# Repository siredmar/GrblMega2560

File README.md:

# GrblMega2560
Shield for GRBL 1.0 based on Arduino Mega 2560

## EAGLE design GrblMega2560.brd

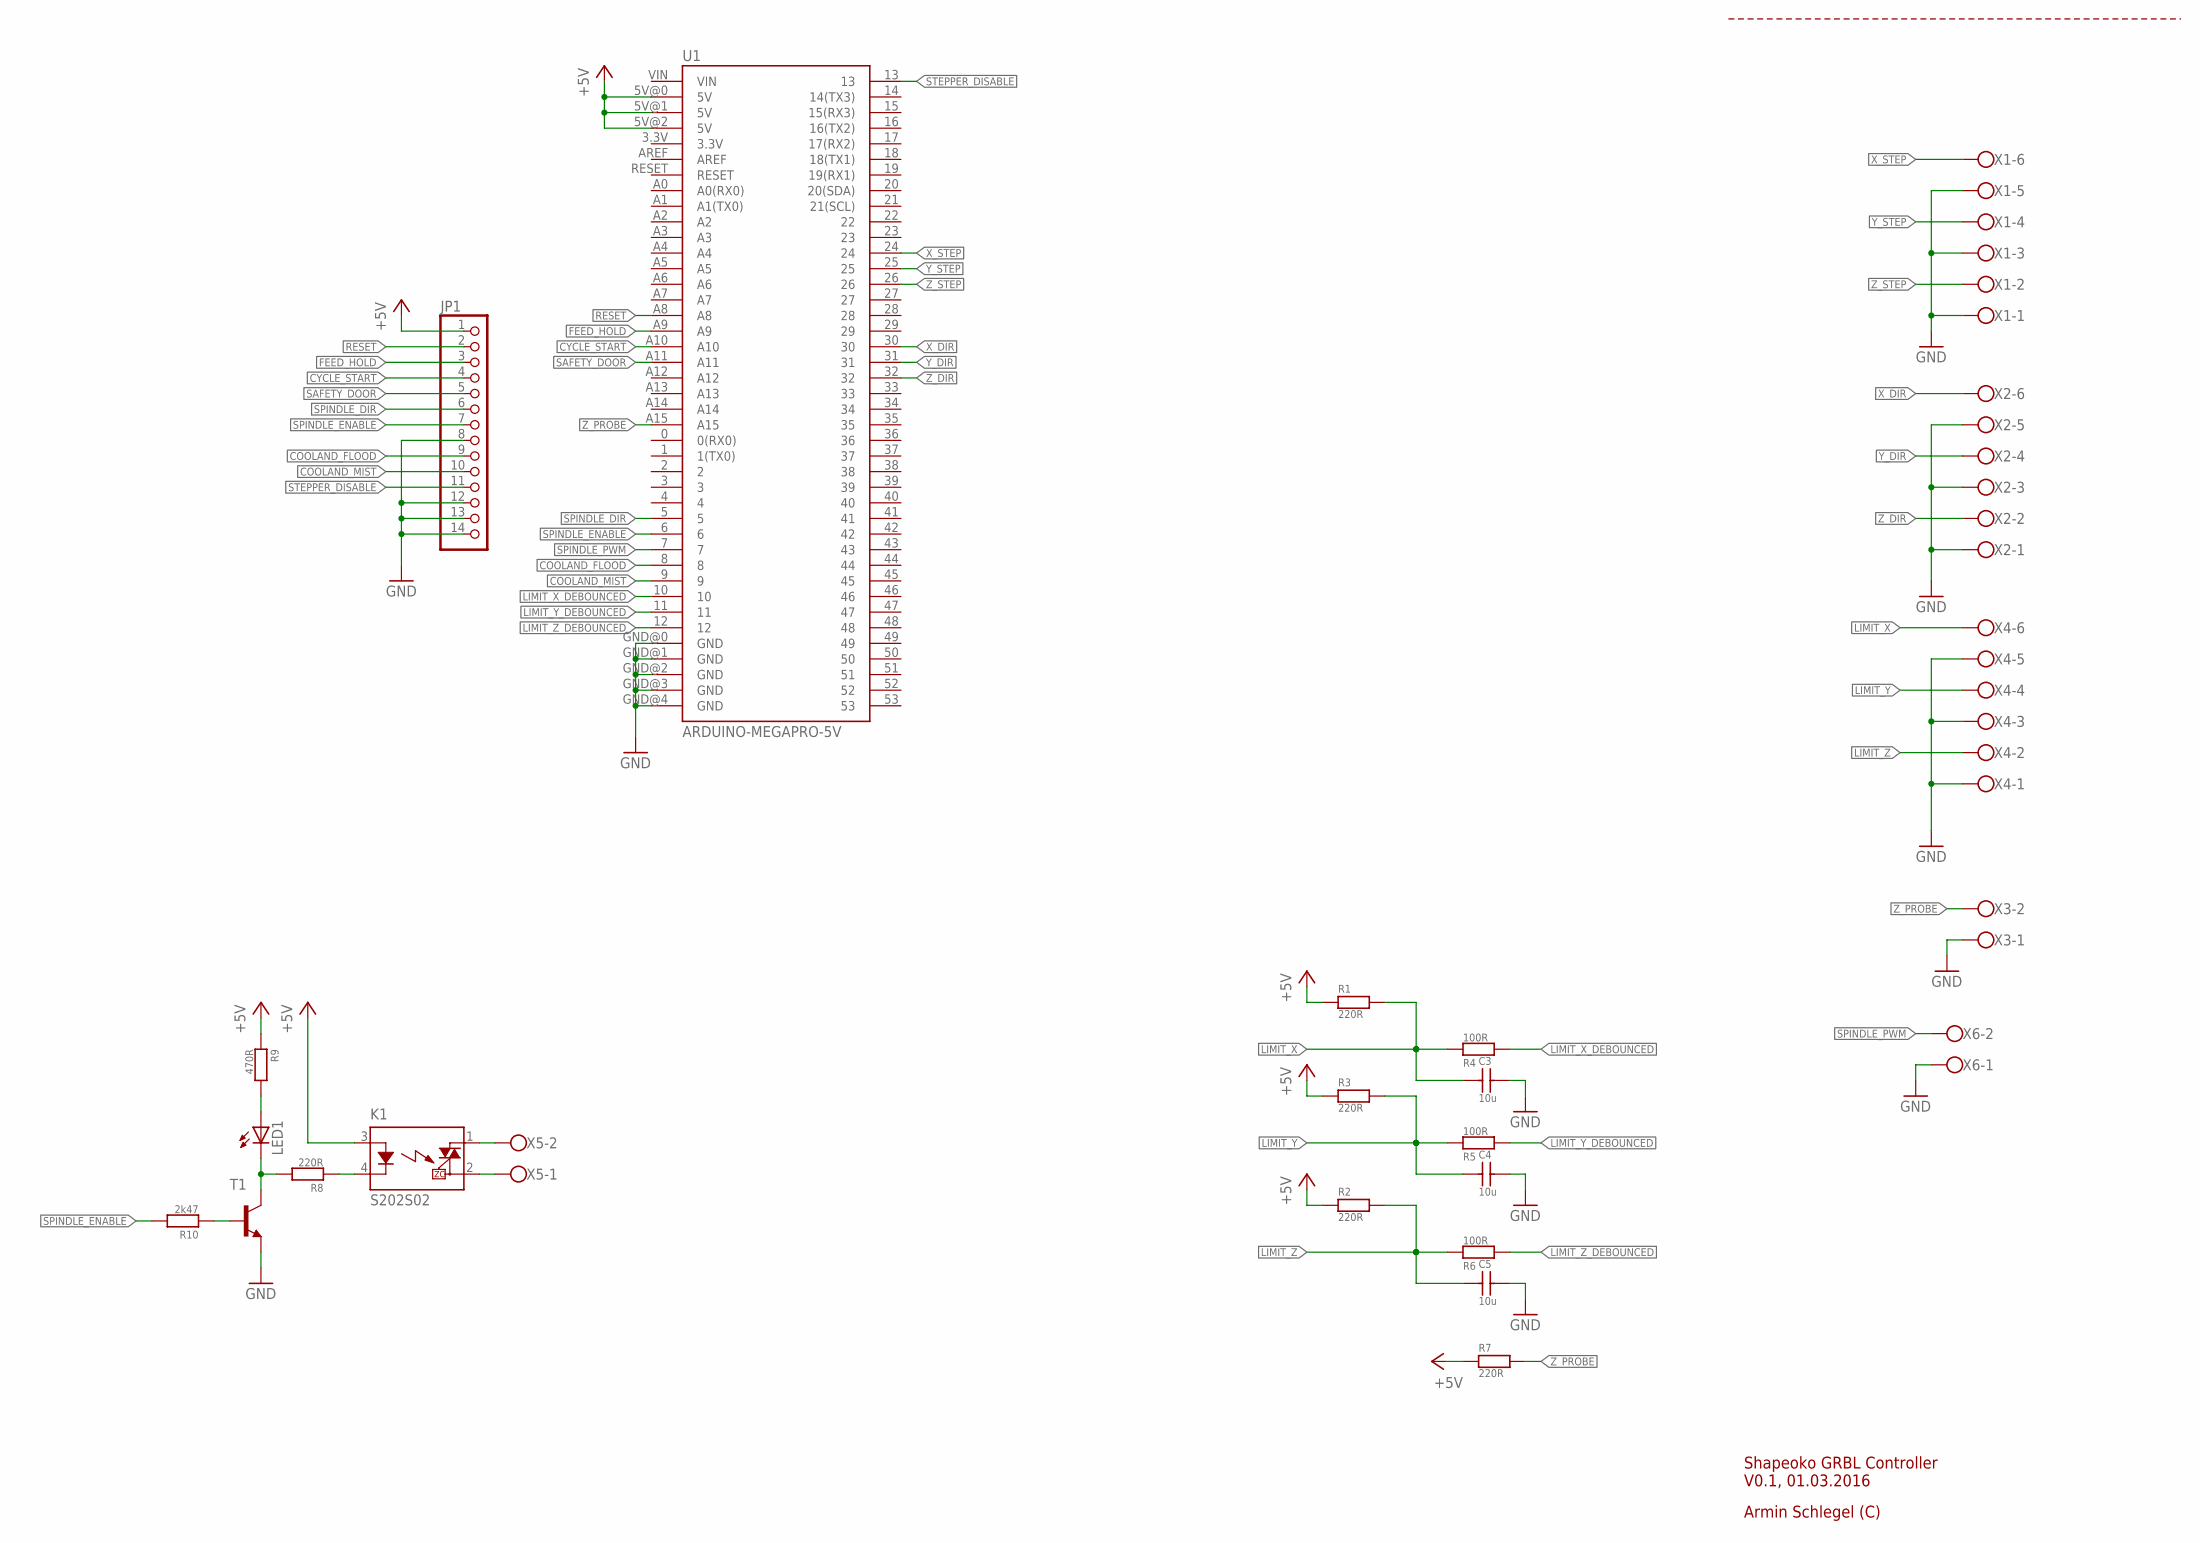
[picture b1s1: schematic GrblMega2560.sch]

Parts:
C3, C4, C5: 10u; C0805
JP1: PINHD-1X14; 1X14
K1: S202S02
LED1: LED3MM
R1, R2, R3, R7, R8: 220R; R0603
R4, R5, R6: 100R; R0603
R9: 470R; R0603
R10: 2k47; R0603
T1: BC847-NPN-SOT23-BEC; SOT23-BEC
U1: ARDUINO-MEGAPRO-5V; ARDUINO_MEGA-PRO-5V
X1, X2, X4: W237-136
X3, X5, X6: W237-102

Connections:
+5V: JP1.1, K1.3 (A), R1.1, R2.1, R3.1, R7.1, R9.1, U1.5V@0 (5V), U1.5V@1 (5V), U1.5V@2 (5V)
COOLAND_FLOOD: JP1.9, U1.8
COOLAND_MIST: JP1.10, U1.9
CYCLE_START: JP1.4, U1.A10
FEED_HOLD: JP1.3, U1.A9
GND: C3.2, C4.2, C5.2, JP1.8, JP1.12, JP1.13, JP1.14, T1.E, U1.GND@0 (GND), U1.GND@1 (GND), U1.GND@2 (GND), U1.GND@3 (GND), U1.GND@4 (GND), X1.1, X1.3, X1.5, X2.1, X2.3, X2.5, X3.1, X4.1, X4.3, X4.5, X6.1
LIMIT_X: C3.1, R1.2, R4.1, X4.6
LIMIT_X_DEBOUNCED: R4.2, U1.10
LIMIT_Y: C4.1, R3.2, R5.1, X4.4
LIMIT_Y_DEBOUNCED: R5.2, U1.11
LIMIT_Z: C5.1, R2.2, R6.1, X4.2
LIMIT_Z_DEBOUNCED: R6.2, U1.12
unnamed: LED1.K (C), R8.2, T1.C
unnamed: LED1.A, R9.2
unnamed: R10.1, T1.B
unnamed: K1.4 (K), R8.1
RESET: JP1.2, U1.A8
SAFETY_DOOR: JP1.5, U1.A11
SPINDLE_DIR: JP1.6, U1.5
SPINDLE_ENABLE: JP1.7, R10.2, U1.6
SPINDLE_N: K1.2 (DS2), X5.1
SPINDLE_P: K1.1 (DS1), X5.2
SPINDLE_PWM: U1.7, X6.2
STEPPER_DISABLE: JP1.11, U1.13
X_DIR: U1.30, X2.6
X_STEP: U1.24, X1.6
Y_DIR: U1.31, X2.4
Y_STEP: U1.25, X1.4
Z_DIR: U1.32, X2.2
Z_PROBE: R7.2, U1.A15, X3.2
Z_STEP: U1.26, X1.2

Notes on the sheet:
Shapeoko GRBL Controller V0.1, 01.03.2016
Armin Schlegel (C)

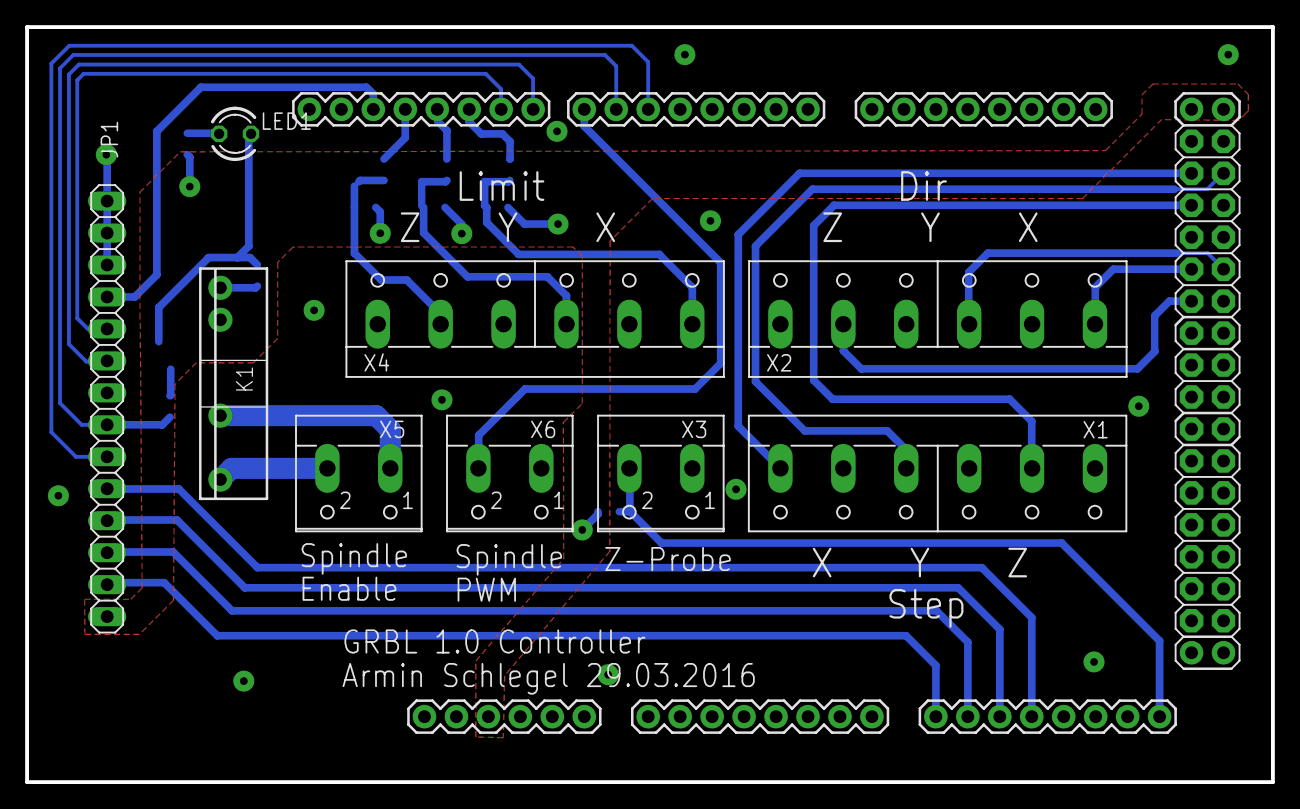
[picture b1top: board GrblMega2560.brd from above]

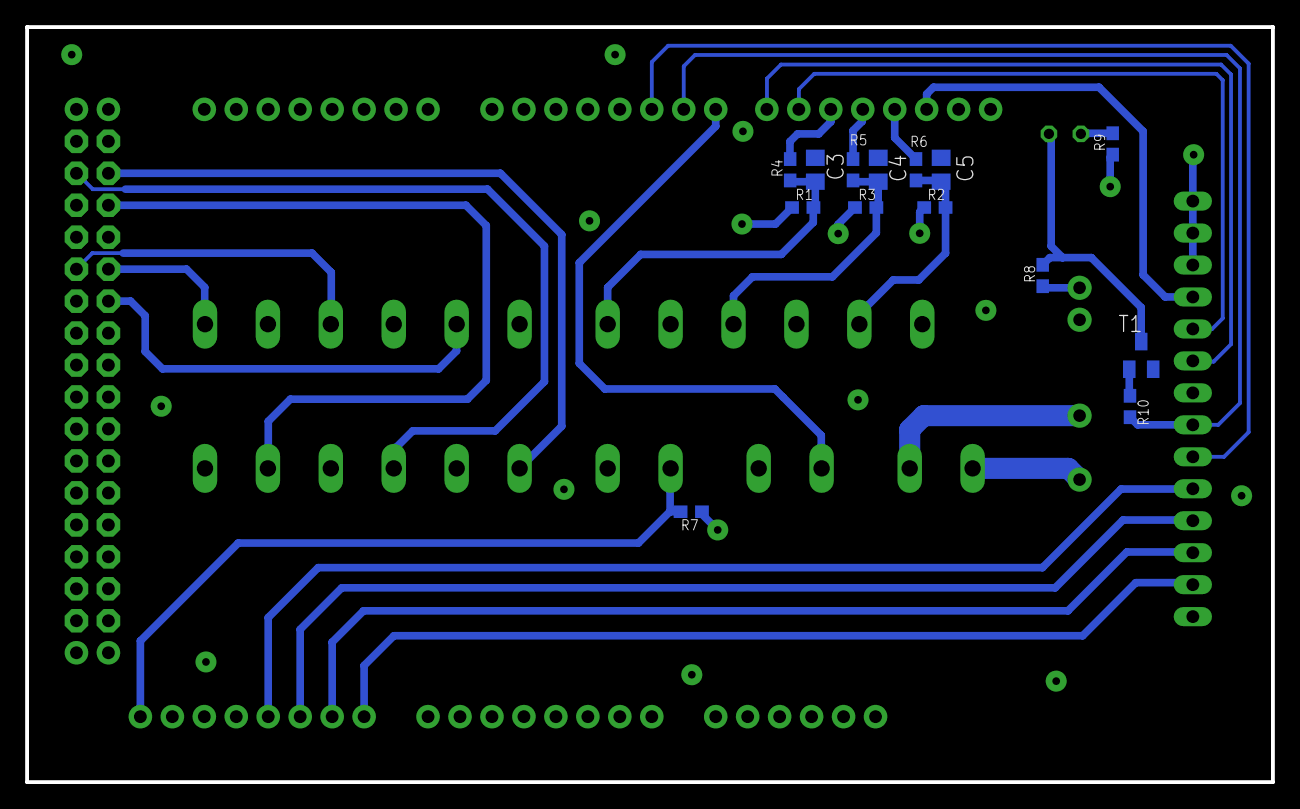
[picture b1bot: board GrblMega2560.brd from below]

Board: 2 copper layers, 99.0 x 60.0 mm, 24 parts (14 on the bottom side), 31 nets.

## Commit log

2016-03-31 First version of GrblMega2560 board

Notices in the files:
parts and their libraries:
SparkFun-Boards: Licensing: Creative Commons ShareAlike 4.0 International - https://creativecommons.org/licenses/by-sa/4.0
